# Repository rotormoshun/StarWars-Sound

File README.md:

# star_wars_arcade_sound_pcb
The source files for the reproduction of the 1983 Star Sars Arcade sound PCB. The PCB is designed with Kicad. This project is complete and the PCB is verified working!

# Folder Structure
* bom - Bill of materials for the sound PCB
* gerbers -The gerber files for the sound PCB
* images - Images used in the development on the sound PCB 
* pcb - The Kicad design files for the sound PCB

# PCB Specifications
* Layers: 2
* Dimensions: 293mm X 227mm
* Different PCB Design: 1
* PCB Thickness: 1.6mm
* Surface Finish: HASL
* Castellated Holes: No
* Copper Weight: 1oz.

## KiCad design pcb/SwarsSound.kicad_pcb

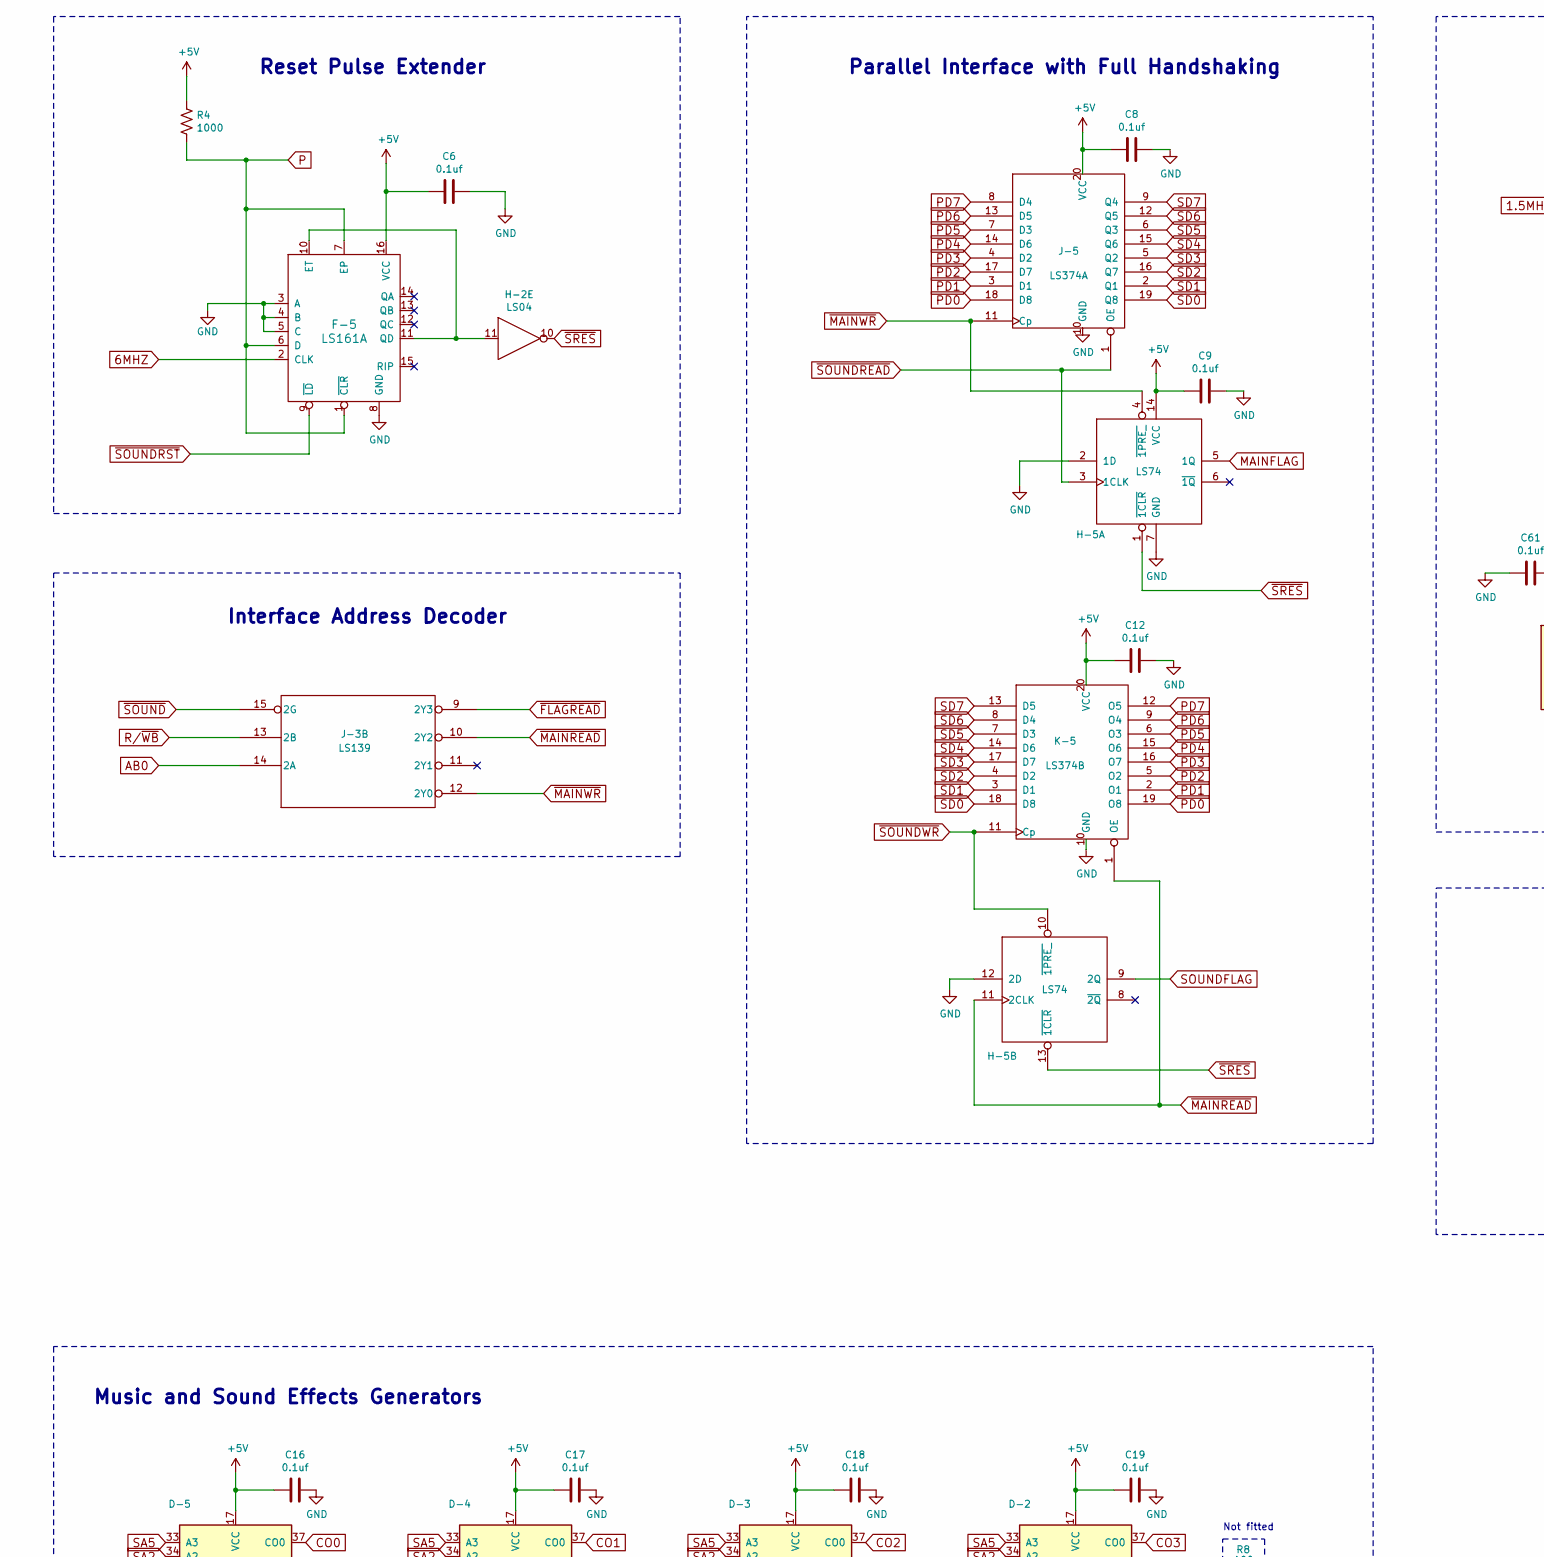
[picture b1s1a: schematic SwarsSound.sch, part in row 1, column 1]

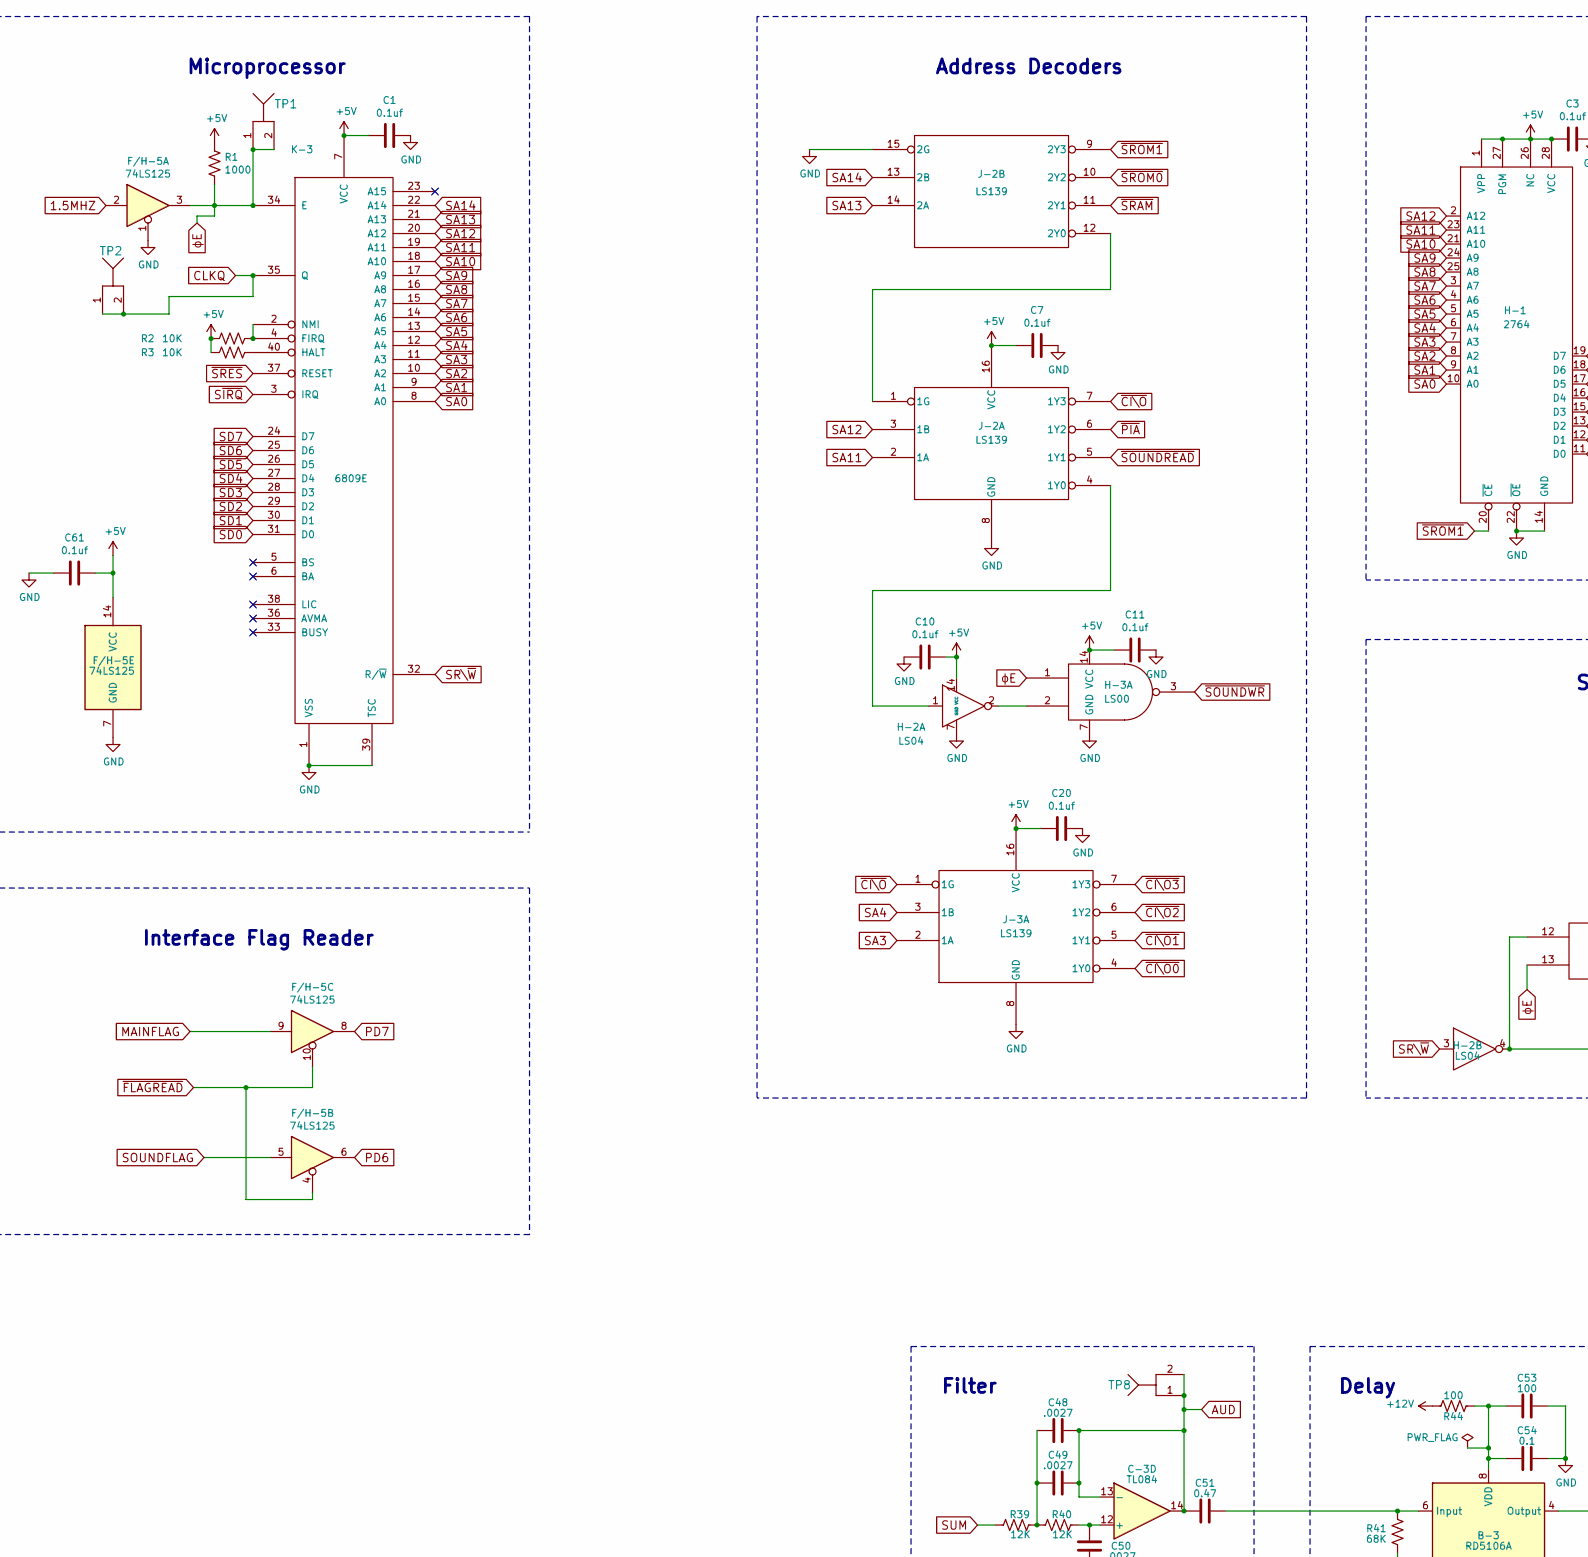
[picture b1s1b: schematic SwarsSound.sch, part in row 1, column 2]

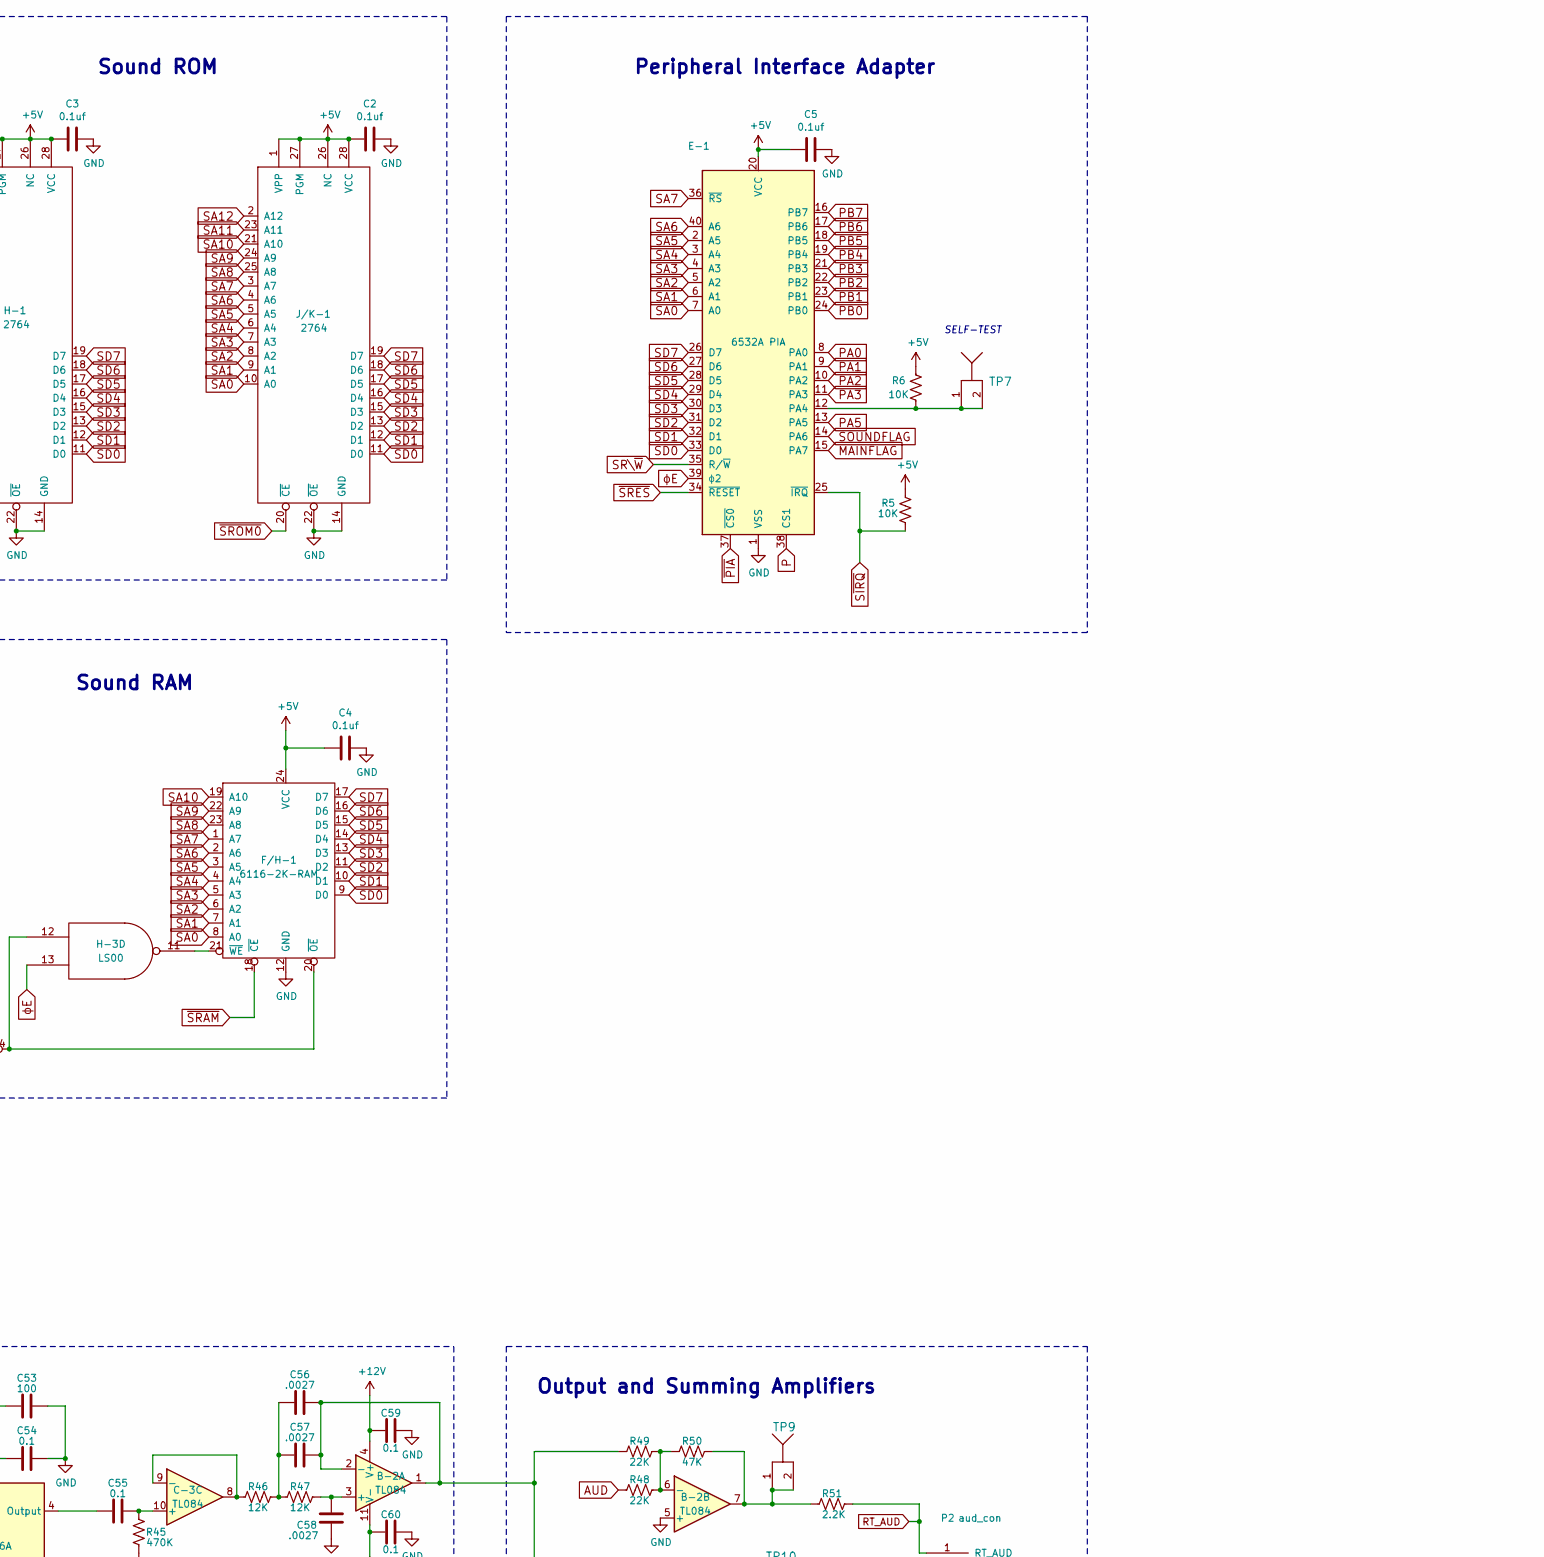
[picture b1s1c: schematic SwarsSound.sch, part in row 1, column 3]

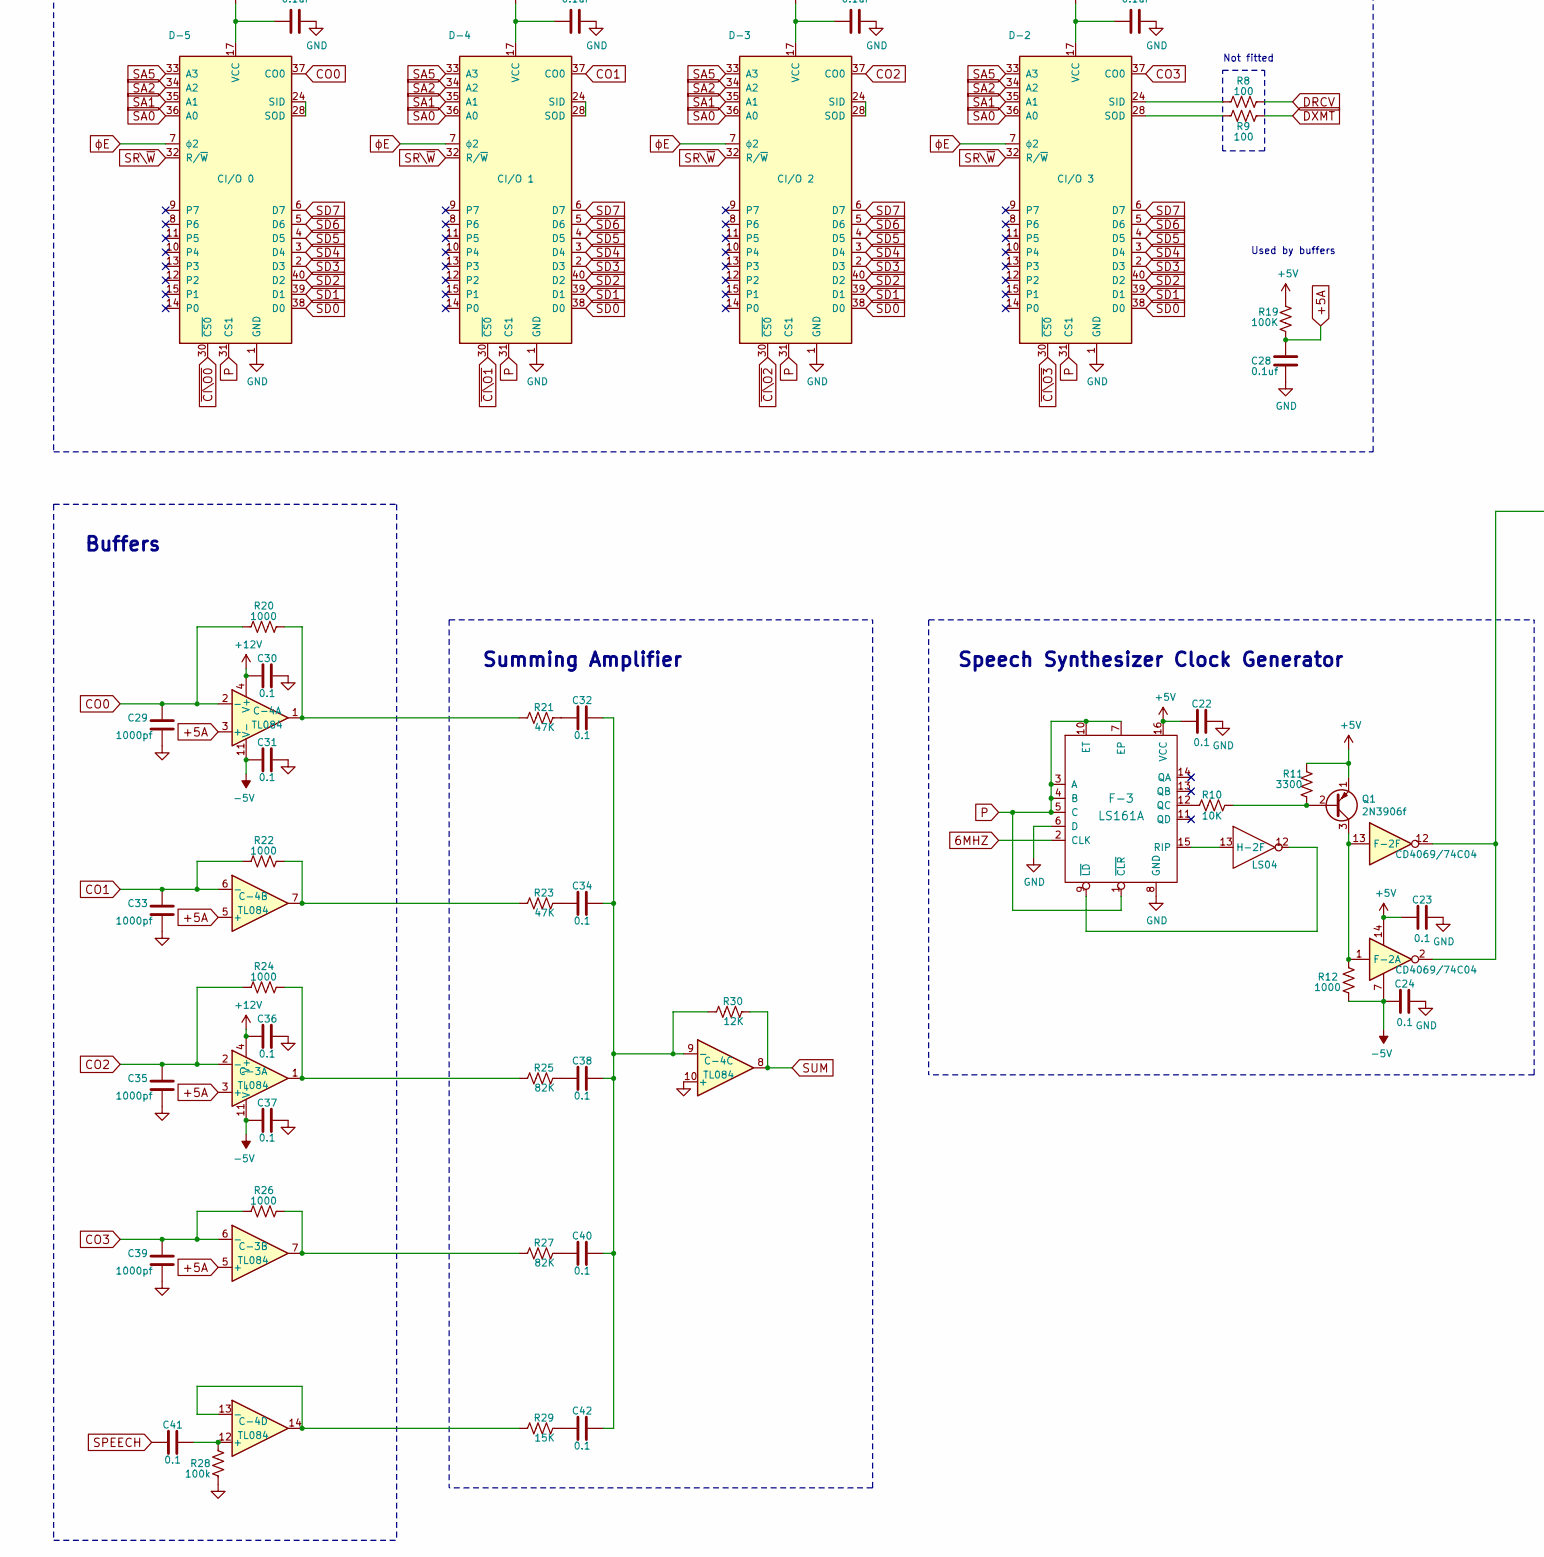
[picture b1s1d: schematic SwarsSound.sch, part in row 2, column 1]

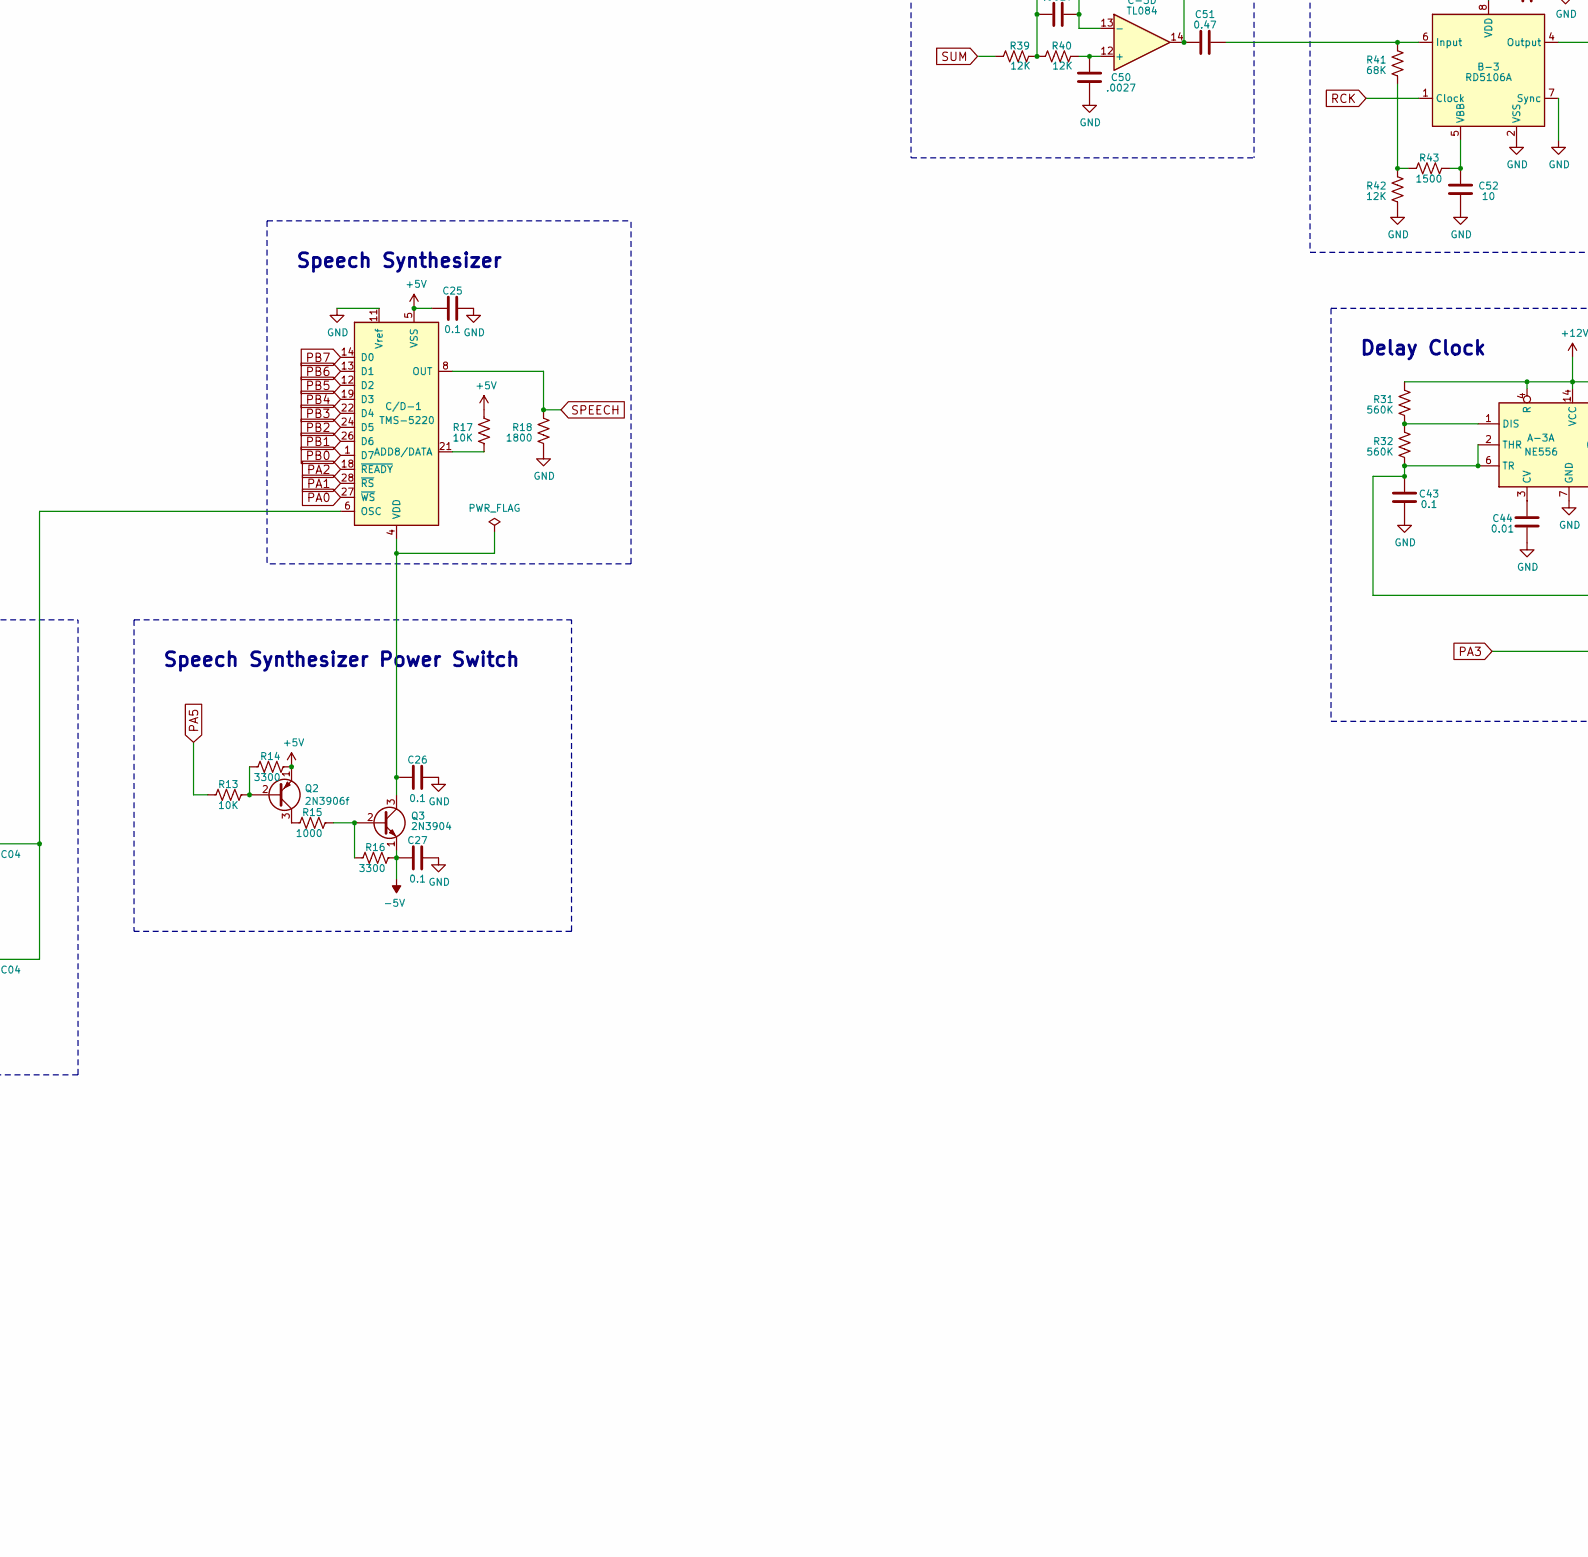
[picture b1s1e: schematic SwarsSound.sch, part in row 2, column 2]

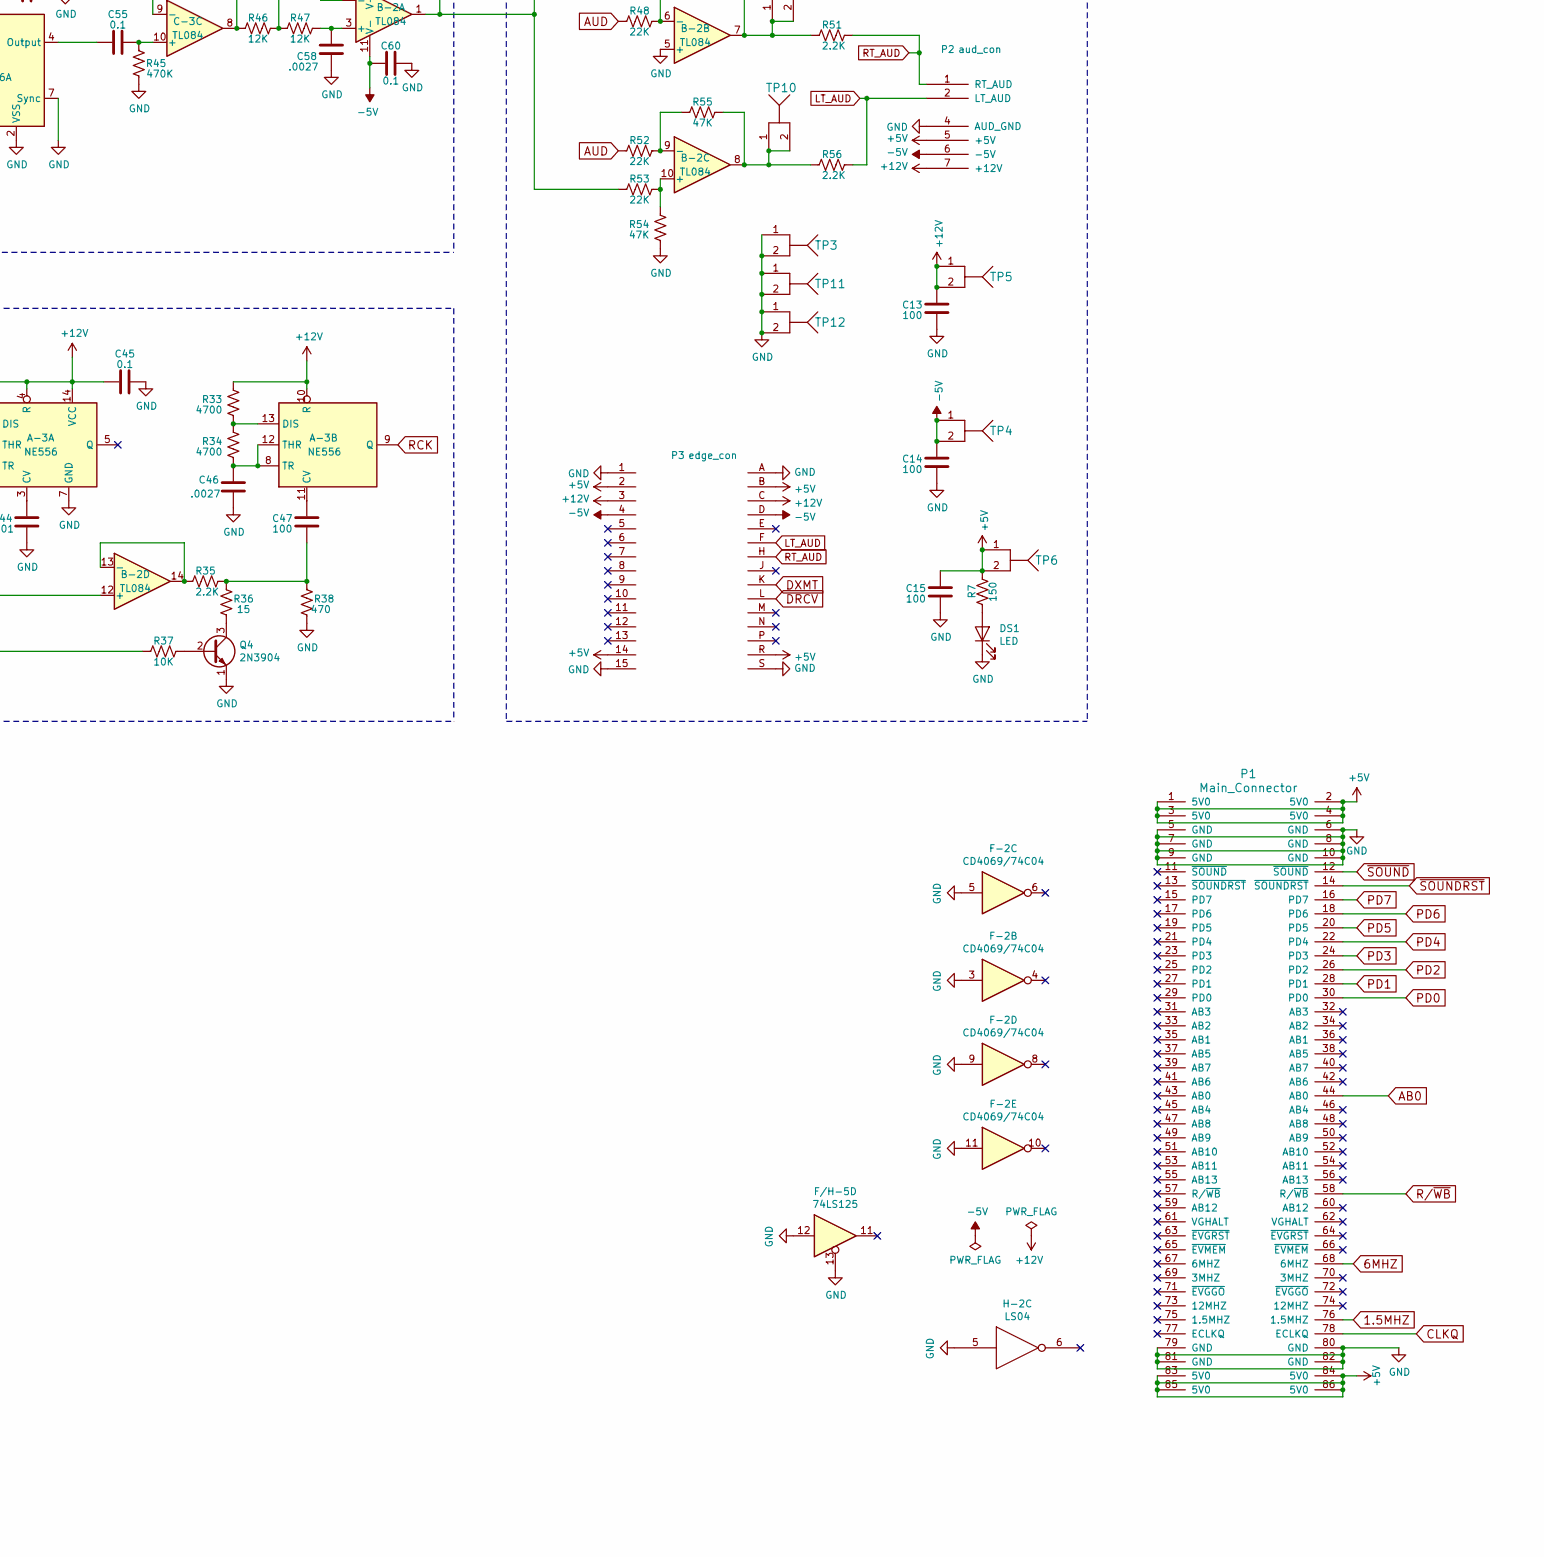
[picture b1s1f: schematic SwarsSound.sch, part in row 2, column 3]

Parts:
A-3: NE556; DIP14
B-2: TL084; DIP14
B-3: RD5106A; DIP8
C1, C2, C3, C4, C5, C6, C7, C8, C9, C10, C11, C12, C16, C17, C18, C19, C20, C28, C61: 0.1uf; GenericComp
C13, C14: 100; CapElec3
C15, C47, C53: 100; CapElec2
C22, C23, C24, C25, C26, C27, C30, C31, C32, C34, C36, C37, C38, C40, C41, C42, C43, C45, C54, C55, C59, C60: 0.1; GenericComp
C29, C33, C35, C39: 1000pf; GenericComp
C44: 0.01; GenericComp
C46, C48, C49, C50, C56, C57, C58: .0027; GenericComp
C51: 0.47; CapElec2
C52: 10; CapElec2
C-3, C-4: TL084; DIP14
C/D-1: TMS-5220; DIP28
D-2: CI/O 3; DDIP40
D-3: CI/O 2; DDIP40
D-4: CI/O 1; DDIP40
D-5: CI/O 0; DDIP40
DS1: LED
E-1: 6532A PIA; DDIP40
F-2: CD4069/74C04; DIP14
F-3, F-5: LS161A; DIP16
F/H-1: 6116-2K-RAM; DDIP24
F/H-5: 74LS125; DIP14
H-1: 2764; DIP28
H-2: LS04; DIP14
H-3: LS00; DIP14
H-5: LS74; DIP14
J-2, J-3: LS139; DIP16
J-5: LS374A; DIP20
J/K-1: 2764; DIP28
K-3: 6809E; DDIP40
K-5: LS374B; DIP20
P1: Main_Connector; J17
P2: aud_con; Aud_Con_7
P3: edge_con; J20
Q1, Q2: 2N3906f; GenericTrans
Q3, Q4: 2N3904; GenericTrans
R1, R4, R12, R15, R20, R22, R24, R26: 1000; GenericComp
R2, R3, R5, R6, R10, R13, R17, R37: 10K; GenericComp
R7: 150; GenericComp
R8, R9, R44: 100; GenericComp
R11, R14, R16: 3300; GenericComp
R18: 1800; GenericComp
R19: 100K; GenericComp
R21, R23, R50, R54, R55: 47K; GenericComp
R25, R27: 82K; GenericComp
R28: 100k; GenericComp
R29: 15K; GenericComp
R30, R39, R40, R42, R46, R47: 12K; GenericComp
R31, R32: 560K; GenericComp
R33, R34: 4700; GenericComp
R35, R51, R56: 2.2K; GenericComp
R36: 15; GenericComp
R38: 470; GenericComp
R41: 68K; GenericComp
R43: 1500; GenericComp
R45: 470K; GenericComp
R48, R49, R52, R53: 22K; GenericComp
TP1, TP2, TP3, TP4, TP5, TP6, TP7, TP8, TP9, TP10, TP11, TP12: TP; TEST_POINT

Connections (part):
1.5MHZ: F/H-5.2, P1.76 (1.5MHZ)
6MHZ: F-3.2 (CLK), F-5.2 (CLK), P1.68 (6MHZ)
+5A: C28.2, C-3.3 (+), C-3.5 (+), C-4.3 (+), C-4.5 (+), R19.2
+5V: C1.2, C2.2, C3.2, C4.2, C5.2, C6.2, C7.2, C8.2, C9.2, C10.1, C11.2, C12.2, C15.2, C16.2, C17.2, C18.2, C19.2, C20.2, C22.1, C23.1, C25.1, C61.1, C/D-1.5 (VSS), D-2.17 (VCC), D-3.17 (VCC), D-4.17 (VCC), D-5.17 (VCC), E-1.20 (VCC), F-2.14, F-3.16 (VCC), F-5.16 (VCC), F/H-1.24 (VCC), F/H-5.14 (VCC), H-1.1 (VPP), H-1.26 (NC), H-1.27 (PGM), H-1.28 (VCC), H-2.14 (VCC), H-3.14 (VCC), H-5.14 (VCC), J-2.16 (VCC), J-3.16 (VCC), J-5.20 (VCC), J/K-1.1 (VPP), J/K-1.26 (NC), J/K-1.27 (PGM), J/K-1.28 (VCC), K-3.7 (VCC), K-5.20 (VCC), P1.1 (5V0), P1.2 (5V0), P1.3 (5V0), P1.4 (5V0), P1.83 (5V0), P1.84 (5V0), P1.85 (5V0), P1.86 (5V0), P2.5 (+5V), P3.2, P3.14, P3.B, P3.R, Q1.1, Q2.1, R1.1, R2.1, R3.1, R4.1, R5.1, R6.1, R7.1, R11.1, R14.2, R17.2, R19.1, TP6.1, TP6.2
+12V: A-3.4 (R), A-3.10 (R), A-3.14 (VCC), B-2.4 (V+), C13.2, C30.1, C36.1, C45.1, C59.1, C-3.4 (V+), C-4.4 (V+), P2.7 (+12V), P3.3, P3.C, R31.2, R33.2, R44.1, TP5.1, TP5.2
-5V: B-2.11 (V-), C14.2, C24.1, C27.1, C31.1, C37.1, C60.1, C-3.11 (V-), C-4.11 (V-), F-2.7, P2.6 (-5V), P3.4, P3.D, Q3.1 (E), R12.2, R16.2, TP4.1, TP4.2
AB0: J-3.14 (2A), P1.44 (AB0)
AUD: C48.2, C49.2, C51.1, C-3.13 (-), C-3.14, R48.2, R52.2, TP8.1, TP8.2
CLKQ: K-3.35 (Q), P1.78 (ECLKQ), TP2.1, TP2.2
CO0: C29.1, C-4.2 (-), D-5.37 (CO0), R20.2
CO1: C33.1, C-4.6 (-), D-4.37 (CO0), R22.2
CO2: C35.1, C-3.2 (-), D-3.37 (CO0), R24.2
CO3: C39.1, C-3.6 (-), D-2.37 (CO0), R26.2
DRCV: P3.L, R8.2
DXMT: P3.K, R9.2
GND: A-3.7 (GND), B-2.5 (+), B-3.2 (VSS), B-3.7 (Sync), C1.1, C2.1, C3.1, C4.1, C5.1, C6.1, C7.1, C8.1, C9.1, C10.2, C11.1, C12.1, C13.1, C14.1, C15.1, C16.1, C17.1, C18.1, C19.1, C20.1, C22.2, C23.2, C24.2, C25.2, C26.2, C27.2, C28.1, C29.2, C30.2, C31.2, C33.2, C35.2, C36.2, C37.2, C39.2, C43.1, C44.1, C45.2, C46.1, C50.1, C52.1, C53.2, C54.2, C58.1, C59.2, C60.2, C61.2, C-4.10 (+), C/D-1.11 (Vref), D-2.1 (GND), D-3.1 (GND), D-4.1 (GND), D-5.1 (GND), DS1.1 (K), E-1.1 (VSS), F-2.3, F-2.5, F-2.9, F-2.11, F-3.6 (D), F-3.8 (GND), F-5.3 (A), F-5.4 (B), F-5.5 (C), F-5.8 (GND), F/H-1.12 (GND), F/H-5.1, F/H-5.7 (GND), F/H-5.12, F/H-5.13, H-1.14 (GND), H-1.22 (~OE), H-2.5, H-2.7 (GND), H-3.7 (GND), H-5.2 (1D), H-5.7 (GND), H-5.12 (2D), J-2.8 (GND), J-2.15 (2G)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
LT_AUD: P2.2 (LT_AUD), P3.F, R56.1
MAINFLAG: E-1.15 (PA7), F/H-5.9, H-5.5 (1Q)
unnamed: A-3.1 (DIS), R31.1, R32.2
unnamed: A-3.2 (THR), A-3.6 (TR), B-2.12 (+), C43.2, R32.1
unnamed: A-3.3 (CV), C44.2
unnamed: A-3.11 (CV), C47.2
unnamed: A-3.8 (TR), A-3.12 (THR), C46.2, R34.1
unnamed: A-3.13 (DIS), R33.1, R34.2
unnamed: B-2.1, B-2.2 (-), C56.2, C57.2, R49.2, R53.2
unnamed: B-2.3 (+), C58.2, R47.1
unnamed: B-2.6 (-), R48.1, R49.1, R50.2
unnamed: B-2.7, R50.1, R51.2, TP9.1, TP9.2
unnamed: B-2.8, R55.1, R56.2, TP10.1, TP10.2
unnamed: B-2.9 (-), R52.1, R55.2
unnamed: B-2.10 (+), R53.1, R54.2
unnamed: B-2.13 (-), B-2.14, R35.2
unnamed: B-3.4 (Output), C55.1
unnamed: B-3.5 (VBB), C52.2, R43.1
unnamed: B-3.6 (Input), C51.2, R41.2
unnamed: B-3.8 (VDD), C53.1, C54.1, R44.2
unnamed: C32.1, R21.1
unnamed: C34.1, R23.1
unnamed: C38.1, R25.1
unnamed: C40.1, R27.1
unnamed: C42.1, R29.1
unnamed: C47.1, R35.1, R36.2, R38.2
unnamed: C48.1, C49.1, R39.1, R40.2
unnamed: C56.1, C57.1, R46.1, R47.2
unnamed: C-3.1, R24.1, R25.2
unnamed: C-3.7, R26.1, R27.2
unnamed: C-3.8, C-3.9 (-), R46.2
unnamed: C55.2, C-3.10 (+), R45.2
unnamed: C50.2, C-3.12 (+), R40.1
unnamed: C-4.1, R20.1, R21.2
unnamed: C-4.7, R22.1, R23.2
unnamed: C32.2, C34.2, C38.2, C40.2, C42.2, C-4.9 (-), R30.2
unnamed: C41.1, C-4.12 (+), R28.2
unnamed: C-4.13 (-), C-4.14, R29.2
unnamed: C26.1, C/D-1.4 (VDD), Q3.3 (C)
unnamed: C/D-1.6 (OSC), F-2.2, F-2.12
unnamed: C/D-1.21 (ADD8/DATA), R17.1
unnamed: D-2.24 (SID), R8.1
unnamed: D-2.28 (SOD), R9.1
unnamed: D-3.24 (SID), D-3.28 (SOD)
unnamed: D-4.24 (SID), D-4.28 (SOD)
unnamed: D-5.24 (SID), D-5.28 (SOD)
unnamed: DS1.2 (A), R7.2
unnamed: E-1.12 (PA4), R6.2, TP7.1, TP7.2
unnamed: F-2.1, F-2.13, Q1.3, R12.1
unnamed: F-3.9 (~LD), H-2.12
unnamed: F-3.12 (QC), R10.1
unnamed: F-3.15 (RIP), H-2.13
unnamed: F-5.10 (ET), F-5.11 (QD), H-2.11
unnamed: F/H-1.20 (~OE), H-2.4, H-3.12
unnamed: F/H-1.21 (~WE), H-3.11
unnamed: H-2.1, J-2.4 (1Y0)
unnamed: H-2.2, H-3.2
unnamed: J-2.1 (1G), J-2.12 (2Y0)
unnamed: K-3.2 (NMI), K-3.4 (FIRQ), R2.2
unnamed: K-3.40 (HALT), R3.2
unnamed: Q1.2, R10.2, R11.2
unnamed: Q2.2, R13.2, R14.1
unnamed: Q2.3, R15.1
unnamed: Q3.2 (B), R15.2, R16.1
unnamed: Q4.2 (B), R37.1
unnamed: Q4.3 (C), R36.1
unnamed: R41.1, R42.2, R43.2
P: D-2.31 (CS1), D-3.31 (CS1), D-4.31 (CS1), D-5.31 (CS1), E-1.38 (CS1), F-3.1 (~CLR), F-3.3 (A), F-3.4 (B), F-3.5 (C), F-3.7 (EP), F-3.10 (ET), F-5.1 (~CLR), F-5.6 (D), F-5.7 (EP), R4.2
PA0: C/D-1.27 (~WS), E-1.8 (PA0)
PA1: C/D-1.28 (~RS), E-1.9 (PA1)
PA2: C/D-1.18 (~READY), E-1.10 (PA2)
PA3: E-1.11 (PA3), R37.2
PA5: E-1.13 (PA5), R13.1
PB0: C/D-1.1 (D7), E-1.24 (PB0)
PB1: C/D-1.26 (D6), E-1.23 (PB1)
PB2: C/D-1.24 (D5), E-1.22 (PB2)
PB3: C/D-1.22 (D4), E-1.21 (PB3)
PB4: C/D-1.19 (D3), E-1.19 (PB4)
PB5: C/D-1.12 (D2), E-1.18 (PB5)
PB6: C/D-1.13 (D1), E-1.17 (PB6)
PB7: C/D-1.14 (D0), E-1.16 (PB7)
PD0: J-5.18 (D8), K-5.19 (O8), P1.30 (PD0)
PD1: J-5.3 (D1), K-5.2 (O1), P1.28 (PD1)
PD2: J-5.17 (D7), K-5.5 (O2), P1.26 (PD2)
PD3: J-5.4 (D2), K-5.16 (O7), P1.24 (PD3)
PD4: J-5.14 (D6), K-5.15 (O6), P1.22 (PD4)
PD5: J-5.7 (D3), K-5.6 (O3), P1.20 (PD5)
PD6: F/H-5.6, J-5.13 (D5), K-5.9 (O4), P1.18 (PD6)
PD7: F/H-5.8, J-5.8 (D4), K-5.12 (O5), P1.16 (PD7)
R/~WB: J-3.13 (2B), P1.58 (R/~WB)
RCK: A-3.9 (Q), B-3.1 (Clock)
RT_AUD: P2.1 (RT_AUD), P3.H, R51.1
SA0: D-2.36 (A0), D-3.36 (A0), D-4.36 (A0), D-5.36 (A0), E-1.7 (A0), F/H-1.8 (A0), H-1.10 (A0), J/K-1.10 (A0), K-3.8 (A0)
SA1: D-2.35 (A1), D-3.35 (A1), D-4.35 (A1), D-5.35 (A1), E-1.6 (A1), F/H-1.7 (A1), H-1.9 (A1), J/K-1.9 (A1), K-3.9 (A1)
SA2: D-2.34 (A2), D-3.34 (A2), D-4.34 (A2), D-5.34 (A2), E-1.5 (A2), F/H-1.6 (A2), H-1.8 (A2), J/K-1.8 (A2), K-3.10 (A2)
SA3: E-1.4 (A3), F/H-1.5 (A3), H-1.7 (A3), J-3.2 (1A), J/K-1.7 (A3), K-3.11 (A3)
SA4: E-1.3 (A4), F/H-1.4 (A4), H-1.6 (A4), J-3.3 (1B), J/K-1.6 (A4), K-3.12 (A4)
SA5: D-2.33 (A3), D-3.33 (A3), D-4.33 (A3), D-5.33 (A3), E-1.2 (A5), F/H-1.3 (A5), H-1.5 (A5), J/K-1.5 (A5), K-3.13 (A5)
SA6: E-1.40 (A6), F/H-1.2 (A6), H-1.4 (A6), J/K-1.4 (A6), K-3.14 (A6)
SA7: E-1.36 (~RS), F/H-1.1 (A7), H-1.3 (A7), J/K-1.3 (A7), K-3.15 (A7)
SA8: F/H-1.23 (A8), H-1.25 (A8), J/K-1.25 (A8), K-3.16 (A8)
SA9: F/H-1.22 (A9), H-1.24 (A9), J/K-1.24 (A9), K-3.17 (A9)
SA10: F/H-1.19 (A10), H-1.21 (A10), J/K-1.21 (A10), K-3.18 (A10)
SA11: H-1.23 (A11), J-2.2 (1A), J/K-1.23 (A11), K-3.19 (A11)
SA12: H-1.2 (A12), J-2.3 (1B), J/K-1.2 (A12), K-3.20 (A12)
SA13: J-2.14 (2A), K-3.21 (A13)
SA14: J-2.13 (2B), K-3.22 (A14)
SD0: D-2.38 (D0), D-3.38 (D0), D-4.38 (D0), D-5.38 (D0), E-1.33 (D0), F/H-1.9 (D0), H-1.11 (D0), J-5.19 (Q8), J/K-1.11 (D0), K-3.31 (D0), K-5.18 (D8)
SD1: D-2.39 (D1), D-3.39 (D1), D-4.39 (D1), D-5.39 (D1), E-1.32 (D1), F/H-1.10 (D1), H-1.12 (D1), J-5.2 (Q1), J/K-1.12 (D1), K-3.30 (D1), K-5.3 (D1)
SD2: D-2.40 (D2), D-3.40 (D2), D-4.40 (D2), D-5.40 (D2), E-1.31 (D2), F/H-1.11 (D2), H-1.13 (D2), J-5.16 (Q7), J/K-1.13 (D2), K-3.29 (D2), K-5.4 (D2)
SD3: D-2.2 (D3), D-3.2 (D3), D-4.2 (D3), D-5.2 (D3), E-1.30 (D3), F/H-1.13 (D3), H-1.15 (D3), J-5.5 (Q2), J/K-1.15 (D3), K-3.28 (D3), K-5.17 (D7)
SD4: D-2.3 (D4), D-3.3 (D4), D-4.3 (D4), D-5.3 (D4), E-1.29 (D4), F/H-1.14 (D4), H-1.16 (D4), J-5.15 (Q6), J/K-1.16 (D4), K-3.27 (D4), K-5.14 (D6)
SD5: D-2.4 (D5), D-3.4 (D5), D-4.4 (D5), D-5.4 (D5), E-1.28 (D5), F/H-1.15 (D5), H-1.17 (D5), J-5.6 (Q3), J/K-1.17 (D5), K-3.26 (D5), K-5.7 (D3)
SD6: D-2.5 (D6), D-3.5 (D6), D-4.5 (D6), D-5.5 (D6), E-1.27 (D6), F/H-1.16 (D6), H-1.18 (D6), J-5.12 (Q5), J/K-1.18 (D6), K-3.25 (D6), K-5.8 (D4)
SD7: D-2.6 (D7), D-3.6 (D7), D-4.6 (D7), D-5.6 (D7), E-1.26 (D7), F/H-1.17 (D7), H-1.19 (D7), J-5.9 (Q4), J/K-1.19 (D7), K-3.24 (D7), K-5.13 (D5)
SOUNDFLAG: E-1.14 (PA6), F/H-5.5, H-5.9 (2Q)
SPEECH: C41.2, C/D-1.8 (OUT), R18.2
SR\~W: D-2.32 (R/~W), D-3.32 (R/~W), D-4.32 (R/~W), D-5.32 (R/~W), E-1.35 (R/~W), H-2.3, K-3.32 (R/~W)
SUM: C-4.8, R30.1, R39.2
S~IRQ: E-1.25 (~IRQ), K-3.3 (IRQ), R5.2
~CI\O: J-2.7 (1Y3), J-3.1 (1G)
~CI\O0: D-5.30 (~CS0), J-3.4 (1Y0)
~CI\O1: D-4.30 (~CS0), J-3.5 (1Y1)
~CI\O2: D-3.30 (~CS0), J-3.6 (1Y2)
~CI\O3: D-2.30 (~CS0), J-3.7 (1Y3)
~FLAGREAD: F/H-5.4, F/H-5.10, J-3.9 (2Y3)
~MAINREAD: H-5.11 (2CLK), J-3.10 (2Y2), K-5.1 (OE)
~MAINWR: H-5.4 (~1PRE_), J-3.12 (2Y0), J-5.11 (Cp)
~PIA: E-1.37 (~CS0), J-2.6 (1Y2)
~SOUND: J-3.15 (2G), P1.12 (~SOUND)
~SOUNDREAD: H-5.3 (1CLK), J-2.5 (1Y1), J-5.1 (OE)
~SOUNDRST: F-5.9 (~LD), P1.14 (~SOUNDRST)
~SOUNDWR: H-3.3, H-5.10 (~1PRE_), K-5.11 (Cp)
~SRAM: F/H-1.18 (~CE), J-2.11 (2Y1)
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
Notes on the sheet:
Peripheral Interface Adapter
Filter
Delay
Output and Summing Amplifiers
Delay Clock
Sound RAM
Speech Synthesizer Clock Generator
Reset Pulse Extender
Interface Address Decoder
Parallel Interface with Full Handshaking
Microprocessor
Interface Flag Reader
Address Decoders
Sound ROM
Music and Sound Effects Generators
Used by buffers
SELF-TEST
Buffers
Summing Amplifier
Speech Synthesizer
Speech Synthesizer Power Switch
Not fitted

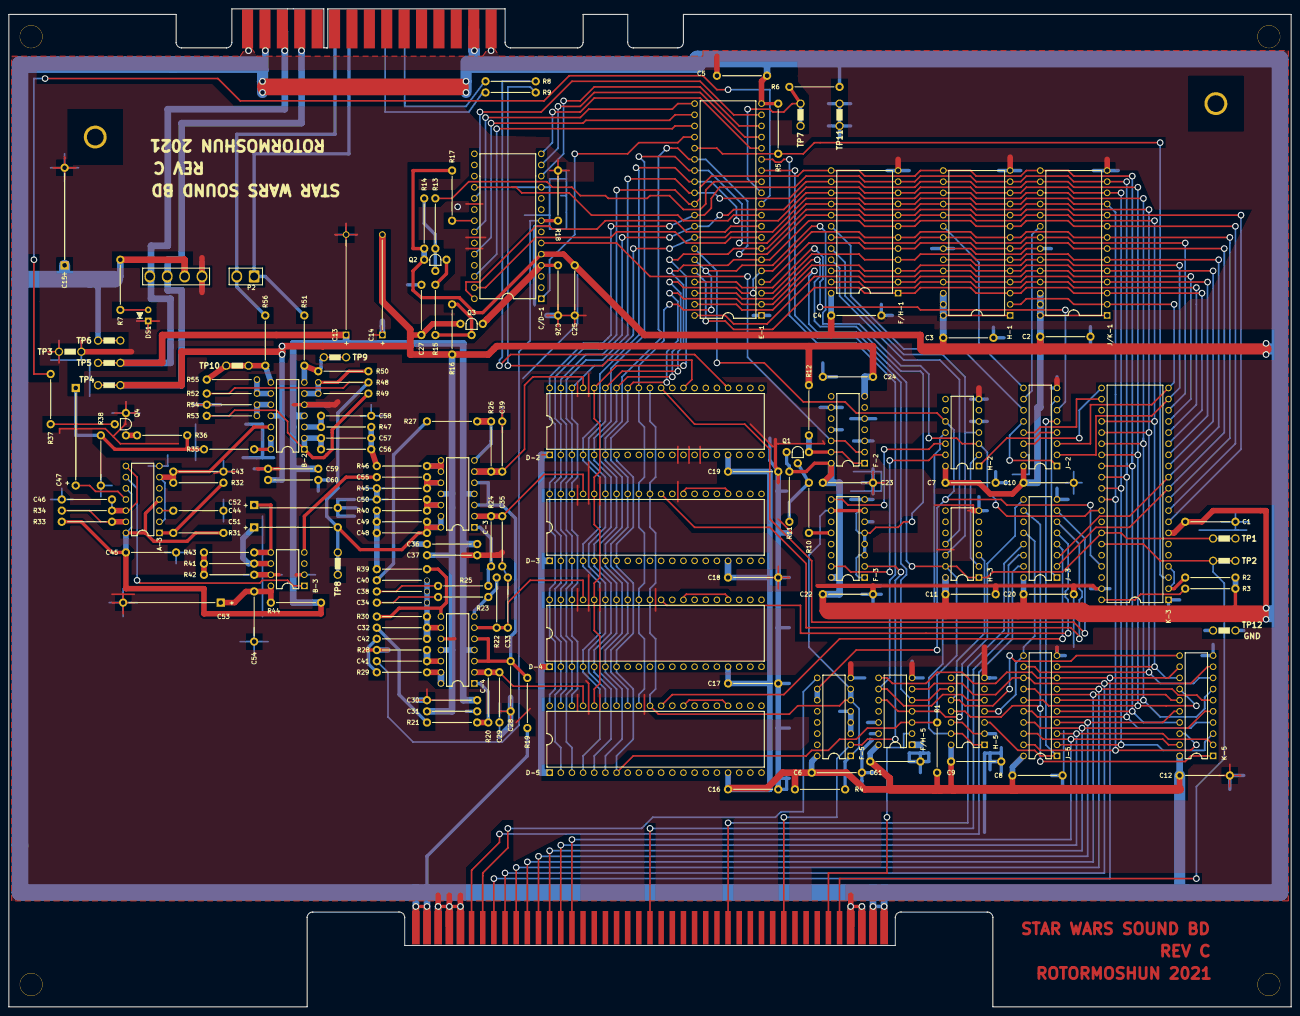
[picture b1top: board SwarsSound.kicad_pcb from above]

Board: 2 copper layers, 292.1 x 227.3 mm, 162 parts (1 on the bottom side), 154 nets.

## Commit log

2021-06-28 Joint session
    Added footprints and plopped chips on nonexistent board.
2021-06-28 Moved a spot
2021-06-28 Began board layout
2021-06-29 Finished chip layout
2021-07-01 test
2021-07-01 next push
2021-07-02 Added TPs and large caps
2021-07-02 right to left to C14 Placed
2021-07-03 All components placed
2021-07-03 Routed some traces
    Couldn't help myself
2021-07-04 Added some traces
2021-07-04 More traces 15 MM
    Make all traces 15MM instead of Default, choose from menu
2021-07-06 thickened POKEY traces
    made them too thin while learning
2021-07-06 ROM and RAM buses
    Not complete
2021-07-06 fixes
    fixed RAM (pin '28' -> 24) and finished RAM/ROM data bus.
2021-07-06 more traces
2021-07-08 adding scans
2021-07-09 more scan footprints
2021-07-10 More traces on top done
2021-07-11 More traces completed
2021-07-11 more traces on bottom completed
2021-07-11 huh?
2021-07-14 Verified spacing and added some traces
2021-07-14 more traces done
2021-07-15 Modified some traces
2021-07-16 Even more traces
2021-07-17 Fixed some traces
2021-07-17 all traces done
2021-07-19 Completed the back of the PCB
2021-07-26 Finished top layer traces
2021-07-26 Added top layer
2021-07-27 Started the BOM
2021-07-27 Finished the top layer plane
2021-07-28 Silkscreen updated
2021-07-28 Finished PCB
2021-07-28 Added gerber files
2021-08-07 Board Tested and Working
    Board built, tested and working
2021-11-09 Updated BOM and test points
2021-11-09 Completed the BOM
2021-11-12 Changed R28 value from 1k to 100k in schematic and BOM
2022-02-19 Updated the file structure and added a readme file
